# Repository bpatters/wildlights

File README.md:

# wildlights
Wild Lights LED controller

This project is a prototype and has been worked on primarily as a learning project. It is not "release" quality in any way
shape or form.

This project has multiple pieces:
- eagle/ledcontroller
  - The Eagle files for the circuit board for the LED controller.
- nrfworksapce 
  - The Workspace project for the firmware for the NRF51822
- xcode/wildlights 
  - The iOS software prototype to test the BLE connection to the board and animations.
- Parts List
  -  BLE_4.0_LED_Head_Unit_PartList.ods

The Fusion 360 models to print the connectors and cases are not part of this project, still thinking about the best way to share
them.

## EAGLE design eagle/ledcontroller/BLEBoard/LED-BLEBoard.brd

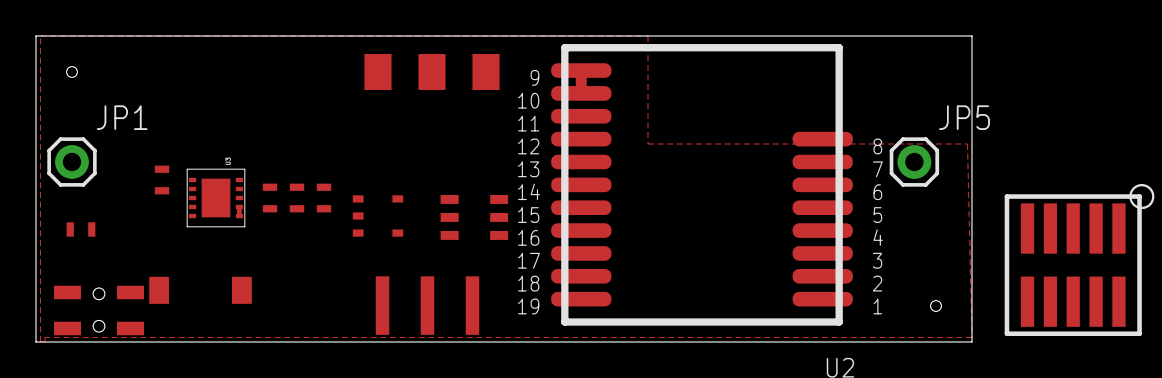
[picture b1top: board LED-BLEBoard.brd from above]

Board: 2 copper layers, 52.0 x 17.0 mm, 18 parts (0 on the bottom side), 13 nets.

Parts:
C1, C2, C3, C4: 22uF; C1.6X0.8
JP1, JP5: M01PTH; 1X01
JP2, JP3, JP4: M01SMD-4.5X1.5; PAD-1.5X4.5
L1: 1UH; SRP5030T
U1: FTSH-105-01-F-DV-ND; FTSH-105-01-XXX-DV-K
U2: RFD22301
U3: TPS61232; VSON10
U5: SC-74A-5PIN
U$1: MM800
U$2: TXS0101TXS0101DBVR; TXS0101DBVR
U$3: PTS840; PTS840GK
U$4: MCR03ERTJ103; C1.6X0.8

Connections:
3.3V: U1.VTREF, U2.13, U5.P$5, U$2.P$1, U$2.P$5, U$4.IN
GND: C1.IN, C2.IN, C3.IN, C4.IN, JP5.1, U1.GND, U1.GND5, U2.1, U2.2, U2.8, U2.9, U2.10, U2.12, U2.18, U2.19, U3.P$11, U5.P$2, U$1.P$3, U$2.P$2, U$3.P$1
GPIO2: U2.3, U$2.P$3
GPIO4: JP2.P$1, U2.5
GPIO5: JP3.P$1, U2.6
GPIO6: JP4.P$1, U2.7
unnamed: U1.SWCLK/TCK, U2.15
unnamed: U2.4, U$3.P$3, U$4.OUT
unnamed: U1.SWDIO/TMS, U2.14
unnamed: U$1.P$2, U$2.P$4
PWIND: L1.P$1, U3.P$1, U3.P$2
PWR5V: C2.OUT, C3.OUT, C4.OUT, U3.P$3, U3.P$4, U3.P$7, U5.P$1, U5.P$3, U$1.P$1, U$2.P$6
VCC: C1.OUT, JP1.1, L1.P$2, U3.P$9, U3.P$10

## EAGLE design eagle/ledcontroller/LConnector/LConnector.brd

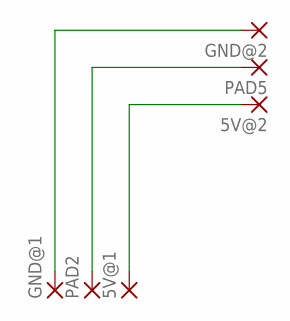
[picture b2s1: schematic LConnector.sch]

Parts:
5V@1, 5V@2: SMD2; SMD1,27-2,54
GND@1, GND@2: SMD2; SMD1,27-2,54
PAD2, PAD5: SMD2; SMD1,27-2,54

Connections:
unnamed: GND@1.1, GND@2.1
unnamed: PAD2.1, PAD5.1
unnamed: 5V@1.1, 5V@2.1

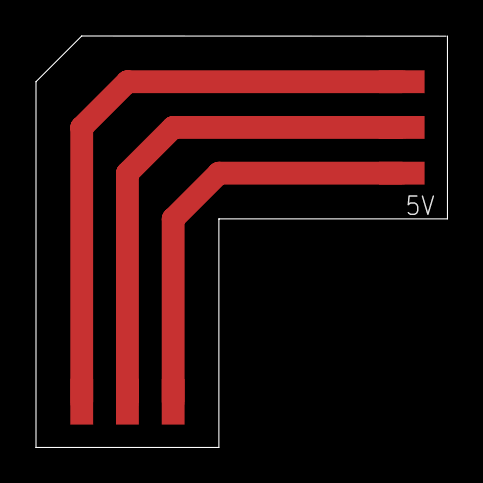
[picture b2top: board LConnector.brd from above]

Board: 2 copper layers, 22.9 x 22.9 mm, 6 parts (0 on the bottom side), 3 nets.

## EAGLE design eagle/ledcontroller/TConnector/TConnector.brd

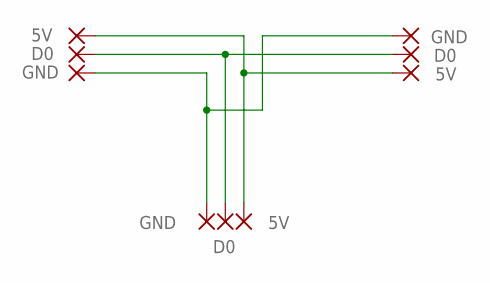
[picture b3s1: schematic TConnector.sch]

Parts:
5V@1, 5V@2, 5V@3: 5V; SMD1,27-2,54
D0: D0; SMD1,27-2,54
GND@1, GND@2, GND@3: GND; SMD1,27-2,54
PAD5, PAD8: D0; SMD1,27-2,54

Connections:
5V: 5V@1.1, 5V@2.1, 5V@3.1
D0: D0.1, PAD5.1, PAD8.1
GND: GND@1.1, GND@2.1, GND@3.1

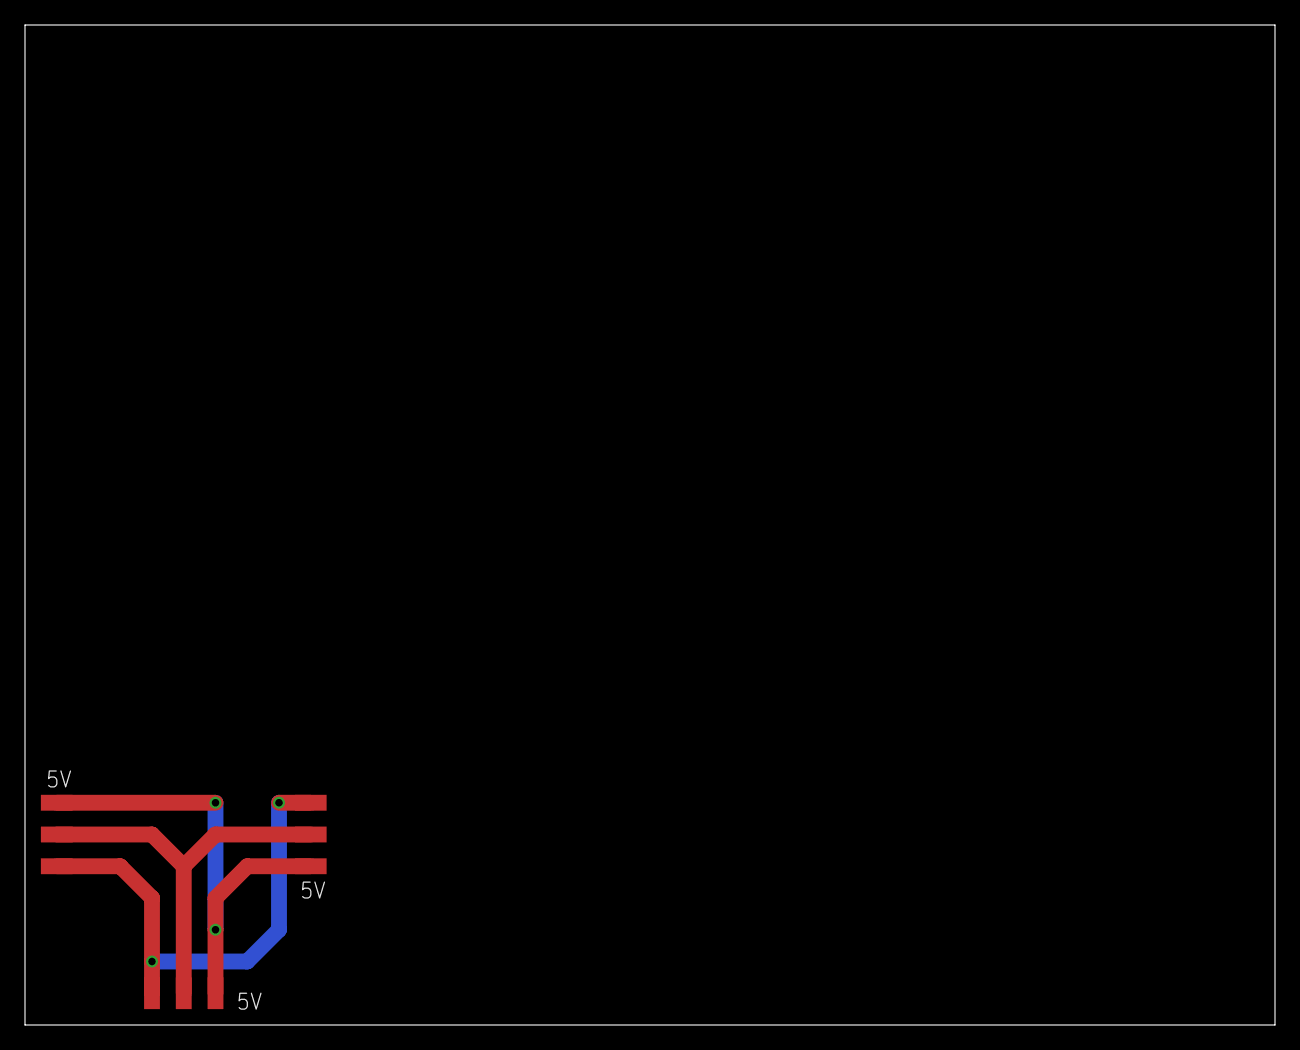
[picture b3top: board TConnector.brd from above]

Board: 2 copper layers, 100.0 x 80.0 mm, 9 parts (0 on the bottom side), 3 nets.

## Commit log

2015-05-18 Initial commit after merging repositories
2015-05-19 BLE service characteristic fixes
2015-05-19 ~20ms min connection interval with 50ms max
2015-05-19 ignore .DS_Store
2015-05-20 Program play on disconnect. other minor updates
2015-05-25 Replaced byte streaming with mini programs. Added support for device settings and sending mini programs to head unit
2015-05-30 BLE Board 0.8. VM changes
2015-05-31 LED 0.8 updates
2015-06-13 V0.8 added switch and re-layout
2015-10-10 beginning
2015-10-12 initial implementation of power on/off button
2018-09-14 add part list

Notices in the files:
parts and their libraries:
SparkFun-Connectors: Licensing: Creative Commons ShareAlike 4.0 International - https://creativecommons.org/licenses/by-sa/4.0
